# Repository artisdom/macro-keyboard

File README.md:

# Macro Keyboard

A Macro keyboard built on ESP32-S3.    

## Features

- Layouts: QMK style
- Macros: fakes multiple key presses on a single key.
- Deep sleep
- Battery level reports
- HID over USB or BLE.
- Support for multiple BLE hosts and specific key layout to switch between them.
- LED backlight with brightness control + effects for BLE actions

## Requirements

### Firmware

Using esp-idf (master branch)

### Hardware

Using Kicad v6.0

## Build

See the esp-idf [instructions](https://docs.espressif.com/projects/esp-idf/en/latest/esp32s3/get-started/index.html) on getting started.

To build:

```shell
idf.py build
```

To flash:

```shell
idf.py flash [-p port_name]
```

To get a console:

```shell
idf.py monitor [-p port_name]
```

### Keyboard Configuration

Each keyboard is defined in it's own subdirectory in the [keyboards](./firmware/keyboards) directory.
This keyboards directory is actually registered as a esp-idf component and will be built as a library and then linked with the [main](./firmware/main) component.

To choose which keyboard to compile for:

```shell
idf.py menuconfig
```
then `Keyboard Configuration` > `Keyboard to build`: Enter the name of the subdirectory for your keyboard.

## Todo

- Cleanup BLE files.
- Create an HID level to create packets to be routed to BLE or USB later on (waiting on esp to finish their esp_hid component).
- QMK features:
	- Make keymap fully compatible with QMK (maybe use the [QMK configurator](https://github.com/qmk/qmk_configurator) or the web api to compile keymaps).
	- Support for more Layer modifiers (one-shot, tap, etc...).
    - Better VIA compatibility (even thought it's a custom fork).
- Better NVS stuff (layouts, configs, ...etc).
- Better Battery reports (when init ble connection use read level).
- Low Battery management: indicator + shutdown.
- Battery optimisations: reduce polling rate when on battery + light sleep + power profiling for leakage currents.
- Clean up HID descriptors to make them common between USB and BLE stacks.
- Better USB deinit (waiting on TinyUSB implementation).
- USB CDC and HID device in parallel to get log outputs in serial port.
- MIDI device?
- Mutiple BLE hosts in parallel? + BLE 5 features?
- If design is kept as BLE only, shift implementation to NimBLE stack (not Bluedroid).
- SPI RAM usage? disabled for now because it was making boot time far too long.

## Issues

- Potential issue when switching BLE host: the hid report array is not propably reset.  
Should not be an issue as BLE host changes are supposed to happen without other keys being pressed.
- BLE local name needs to be less than 15 characters. Otherwise macOS will not show it in the discovery menu.

## License

Firmware and Software: MIT

Hardware: CERN-OHL-W v2

## Docs / Referencs

- ESP-IDF [Guide](https://docs.espressif.com/projects/esp-idf/en/v4.4.2/esp32s3/index.html).
- ESP32-S3 [Datasheet](https://www.espressif.com/sites/default/files/documentation/esp32-s3_datasheet_en.pdf).
- ESP32-S3 [Technical Reference Manual](https://www.espressif.com/sites/default/files/documentation/esp32-s3_technical_reference_manual_en.pdf).
- [TinyS3](https://esp32s3.com/index.html#home) board.
- [Blog](http://blog.komar.be/how-to-make-a-keyboard-the-matrix/) on matrix keyboard design. 
- QMK [keymaps](https://docs.qmk.fm/#/keymap?id=keymap-and-layers) and [layers](https://docs.qmk.fm/#/feature_layers) documentation.
- USB HID [usage tables](https://www.usb.org/sites/default/files/hut1_4.pdf)

### Inspirations

- [QMK](https://github.com/qmk/qmk_firmware/) for AVR devices.
- [MK32](https://github.com/Galzai/MK32) a QMK style firmware for ESP32 devices.

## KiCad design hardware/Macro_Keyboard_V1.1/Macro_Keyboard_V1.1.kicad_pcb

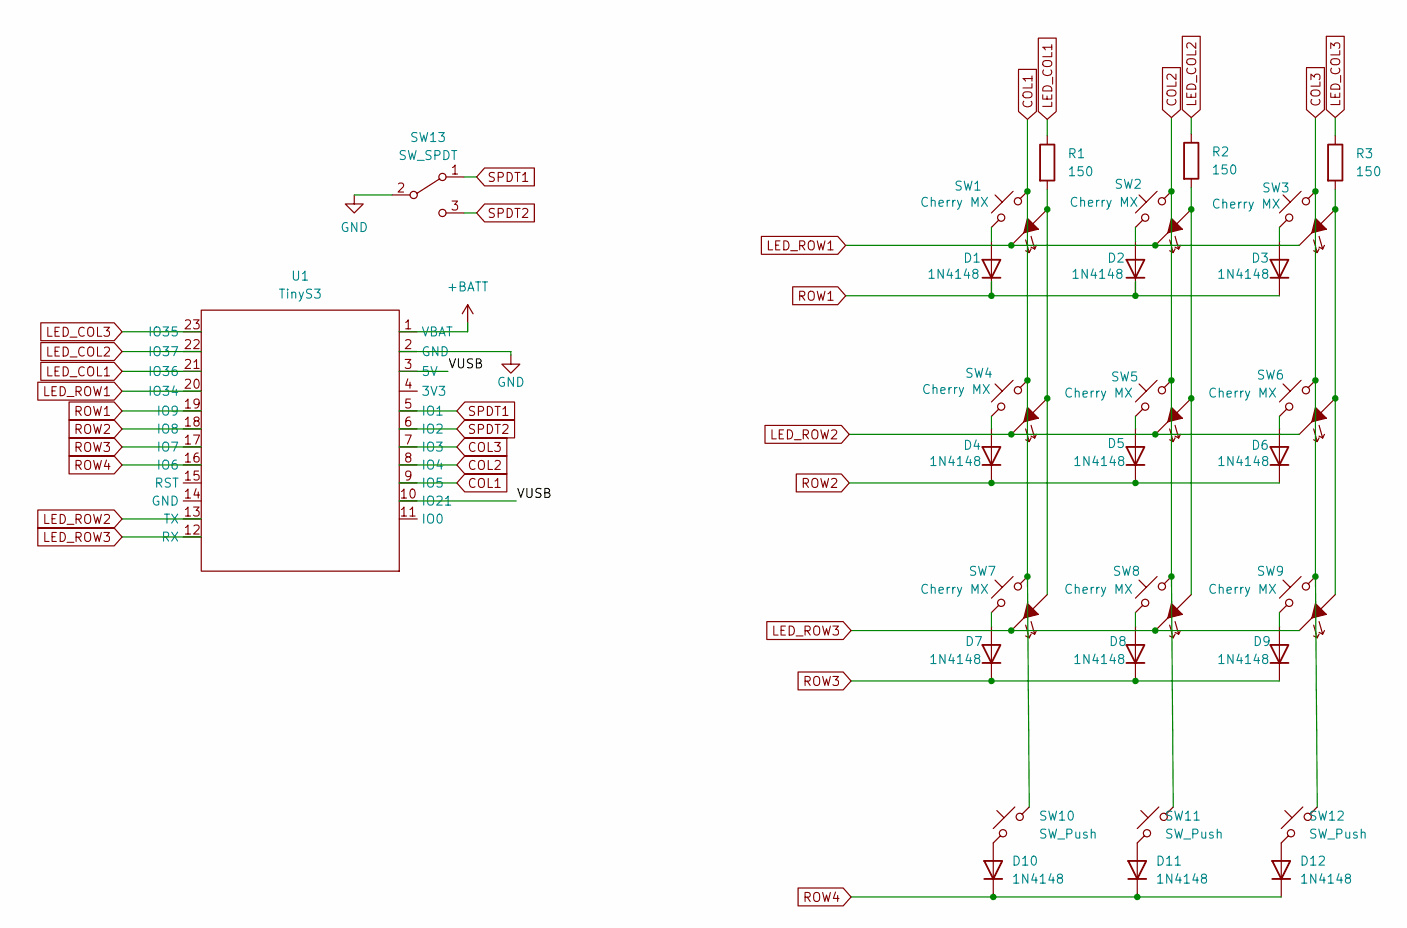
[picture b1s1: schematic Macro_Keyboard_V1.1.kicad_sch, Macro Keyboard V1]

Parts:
D1, D2, D3, D4, D5, D6, D7, D8, D9, D10, D11, D12: 1N4148; D_SOD-123
R1, R2, R3: 150; R_1206_3216Metric_Pad1.30x1.75mm_HandSolder
SW1, SW2, SW3, SW4, SW5, SW6, SW7, SW8, SW9: Cherry MX; CherryMX_1.00u_LED
SW10, SW11, SW12: SW_Push; SW_PUSH_6mm_H7.3mm
SW13: SW_SPDT; SK12D07VG4
U1: TinyS3

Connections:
+BATT: U1.1 (VBAT); also elsewhere on the board
/VUSB: U1.3 (5V), U1.10 (IO21)
COL1: SW1.1, SW4.1, SW7.1, SW10.2, U1.9 (IO5)
COL2: SW2.1, SW5.1, SW8.1, SW11.2, U1.8 (IO4)
COL3: SW3.1, SW6.1, SW9.1, SW12.2, U1.7 (IO3)
GND: SW13.2 (B), U1.2 (GND); also elsewhere on the board
LED_COL1: R1.1, U1.21 (IO36)
LED_COL2: R2.1, U1.22 (IO37)
LED_COL3: R3.1, U1.23 (IO35)
LED_ROW1: SW1.4, SW2.4, SW3.4, U1.20 (IO34)
LED_ROW2: SW4.4, SW5.4, SW6.4, U1.13 (TX)
LED_ROW3: SW7.4, SW8.4, SW9.4, U1.12 (RX)
unnamed: D1.2 (A), SW1.2
unnamed: D2.2 (A), SW2.2
unnamed: D3.2 (A), SW3.2
unnamed: D4.2 (A), SW4.2
unnamed: D5.2 (A), SW5.2
unnamed: D6.2 (A), SW6.2
unnamed: D7.2 (A), SW7.2
unnamed: D8.2 (A), SW8.2
unnamed: D9.2 (A), SW9.2
unnamed: D10.2 (A), SW10.1
unnamed: D11.2 (A), SW11.1
unnamed: D12.2 (A), SW12.1
unnamed: R1.2, SW1.3, SW4.3, SW7.3
unnamed: R2.2, SW2.3, SW5.3, SW8.3
unnamed: R3.2, SW3.3, SW6.3, SW9.3
ROW1: D1.1 (K), D2.1 (K), D3.1 (K), U1.19 (IO9)
ROW2: D4.1 (K), D5.1 (K), D6.1 (K), U1.18 (IO8)
ROW3: D7.1 (K), D8.1 (K), D9.1 (K), U1.17 (IO7)
ROW4: D10.1 (K), D11.1 (K), D12.1 (K), U1.16 (IO6)
SPDT1: SW13.1 (A), U1.5 (IO1)
SPDT2: SW13.3 (C), U1.6 (IO2)

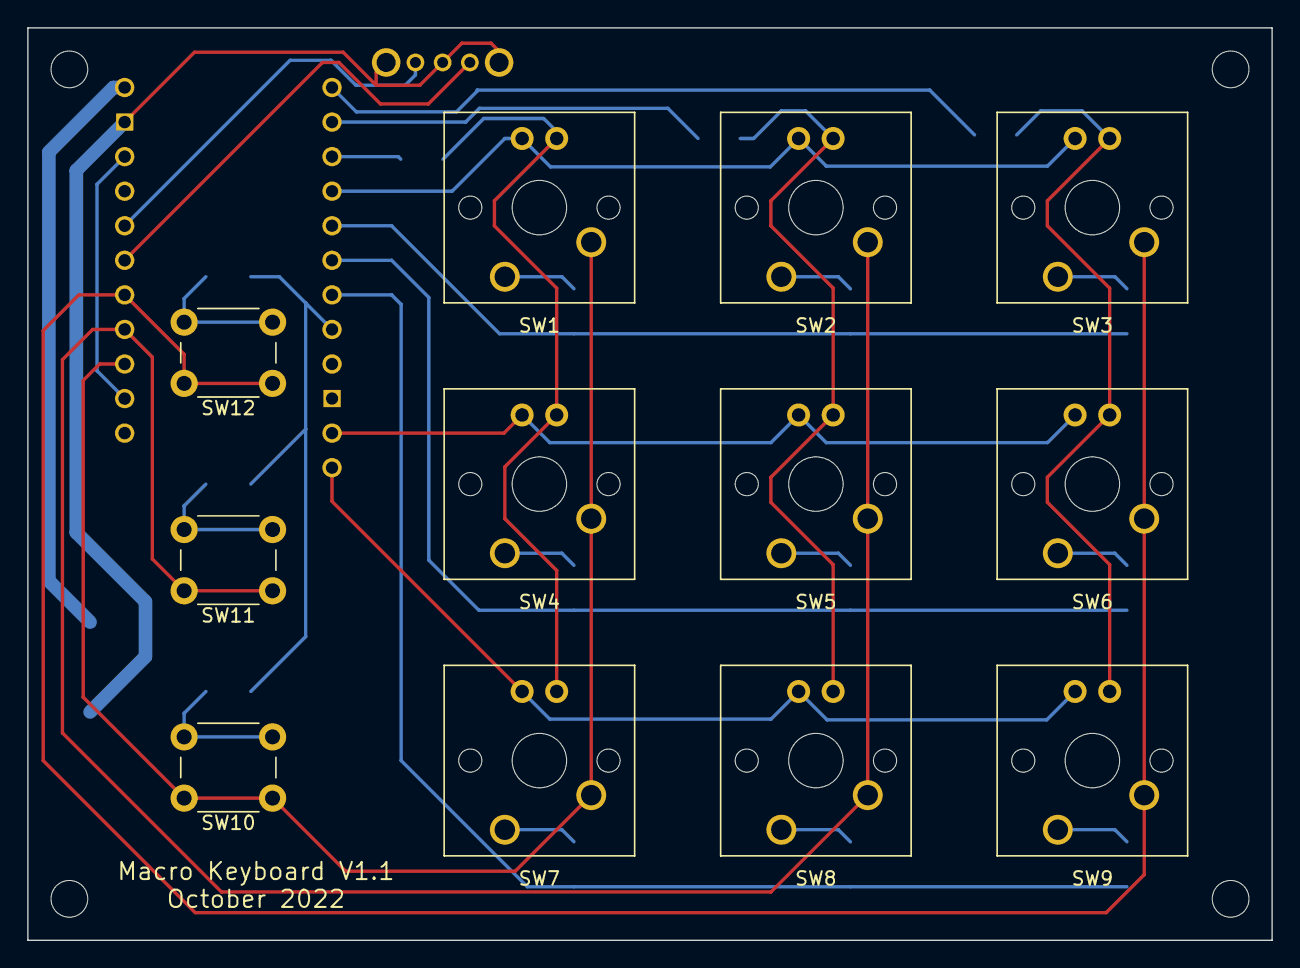
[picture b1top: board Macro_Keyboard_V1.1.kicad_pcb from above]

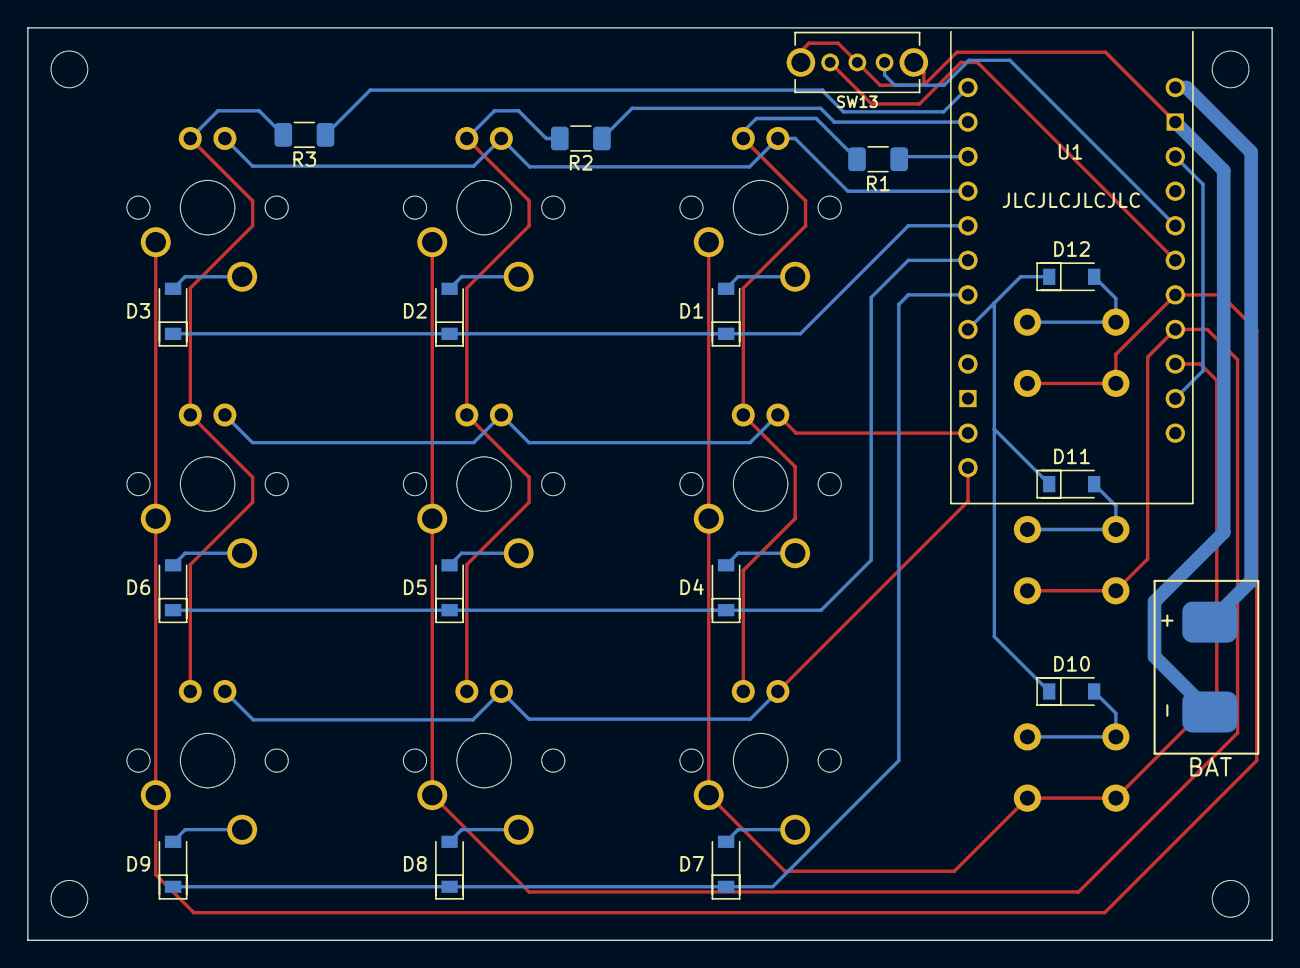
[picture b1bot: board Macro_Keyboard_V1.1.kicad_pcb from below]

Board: 2 copper layers, 91.4 x 67.1 mm, 31 parts (19 on the bottom side), 33 nets.

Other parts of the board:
+: SolderWirePad_1x01_SMD_3x4mm
-: SolderWirePad_1x01_SMD_3x4mm

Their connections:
+BATT: +.1; also elsewhere on the board
GND: -.1; also elsewhere on the board

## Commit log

2022-08-20 Initial commit of a working keyboard with modifiers and BLE
2022-08-20 Added Readme and license files
2022-08-20 Added deep sleep and wakeup with key presses
2022-08-21 Added support for multiple BLE hosts and switch between them
2022-08-23 Preliminary LED driver
2022-08-23 Added support for Esp32S3 chip with logging throught USB
2022-08-27 Updated project files to make it work from clean state
2022-08-28 Added support for HID Consumer control reports
2022-08-28 Updates to keyboard matrix to fit current HW design
2022-08-28 Update to LED matrix config to test for current HW design
2022-08-28 cleanup of the keymap and layouts in it's own separate file
2022-08-29 Added toggle_switch support and refactored with an event handler
2022-08-30 bug fixing
2022-09-01 Added simple battery level reports
2022-09-01 Added usb voltage detection
2022-09-01 Added bluetooth host reset as a keycode
2022-09-02 Fixed BT reset host events
2022-09-04 Migrated to esp-idf master branch
    For development of the HID over USB, will switch to a stable release or branch later
2022-09-05 Added HID over USB
    and added media task to route media/CC reports between BLE and USB
2022-09-07 Added Brightness control on backlight leds
    with special keycodes and events to handle it + each led matrix column uses a separate LEDC channel
2022-09-17 Finally got a tiny effect task for leds based on bluetooth events
2022-09-17 Cleanup RTOS task configs
2022-09-17 Fixed identation
2022-09-19 Modifications to run on V1 hardware
    Extended keymaps + fixed toggle switch events and added debounce in the ISR handler
2022-09-20 Fixed compilation warnings for new ADC driver
2022-09-21 Refactored layering system to make it closer to QMK
2022-09-21 Added layout macro as QMK does for better readability of layers
2022-09-22 Added layer save in nvs
    + refactored keycodes based on QMK
2022-09-22 Fixed led effect driver
    Added CIE1951 linear brightness curve
2022-09-27 Added modifier and shifted symbol macros
    with better modifier handling
2022-09-28 Added a real layering system
    Same as QMK
2022-09-30 Misc improvements to sleep behavious
    Added toggle switch RTC wakeup and better deinit of matrix RTC
2022-10-02 Finalised sleep behaviours
    Added USB cable detection, refactored sleep logic, refactored memory NVS interface
2022-10-02 Added Hardware v1.0
    Changed project layout to account for hardware directories
2022-10-02 Added Hardware v1.1
    Added USB bus voltage to an RTC pin for USB wakeups + Better diode symbol
2022-10-16 Better interface init and deinit
    with task deletion and custom tinyusb task
2022-10-21 Fixed LED bluetooth effects on USB toggle
2022-10-23 Added support for multiple keyboards configurations
    Created keyboards component + small optimisations in cmake build settings
2022-10-24 Added on layer change led effects
2022-10-24 misc improvements and fixes
    Fixed momentary layer effects, Fixed media keys, Added console through USB CDC
2022-10-24 Building keymap for first production unit
2022-10-25 misc refactoring
2022-10-29 Fixed bluetooth advertising
2022-11-07 Added support for VIA
    with USB, command parser and dynamic keymaps
2022-11-07 fixed dynamic layout loading bug
    add misc improvements
2022-12-03 Misc tweaks
    BLE switching and task rate on battery management + uart redirection on boot
2022-12-04 Added esp-idf as a submodule
2022-12-05 Refactored keyboard for recursive macros and better report handling
2022-12-05 Fixed led effects when changing
2022-12-05 Fixed keyboard keymaps configs
2022-12-11 Added oneshot layers
2022-12-11 Added timeouts on oneshot layers
2023-05-01 Added Hardware License
    Cern's weakly reciprocal license
2023-09-24 Added 3d models for all components
2023-09-24 Added new keymap layer for Sublime Texts shortcuts
2023-09-25 Added via custom menu for backlight control
2023-09-29 Non working attempt at getting a cdc device
    with compatibility for restart in bootloader with esptools.py
2023-12-03 Finally able to reboot in bootloader download mode
2023-12-03 Added debug keycodes
2023-12-04 Fix for TinyUSB tud_hid_set_report_cb no being called on VIA packet reception
2023-12-04 Refactored backlight control + added toggle control
2023-12-04 Fixed backlight keycodes
2023-12-04 Support for VIA matrix testing
2023-12-07 Added scripts
    including manifest generation script
2023-12-07 fixed scripts
2023-12-07 CI: first attempt at creating job
2023-12-07 CI: fixed esp target using default
2023-12-07 CI: updated workdir
2023-12-07 CI: add create manigest and artifacts
2023-12-07 CI: fixed multiline python script command
2023-12-07 Updated manifest script path to match job artifacts path
2023-12-07 Added relative path to manifest script
2023-12-08 Added keyboard config directory as a CI variable
2023-12-08 Better keyboard confi variable handling
2023-12-08 Fixed sdkconfig.defaults
2023-12-08 Added gitlab-ci
2023-12-09 Split keyboard configuration for default and dev
2024-01-24 Refactoring of keycodes using separate definitions
2024-01-24 Fixed keymaps
2024-02-04 Updated keycodes for VIA compatibility
2024-02-11 Updated work config
2024-02-25 Fixed battery level on BLE connection
2024-04-13 Fixed BLE host led effects on boot
2024-04-27 Updated Home keyboard keymap
